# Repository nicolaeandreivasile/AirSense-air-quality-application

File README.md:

# AirSense - Air Quality Monitoring Application

## Description
We propose an application that measures the air quality in a specific location by collecting and analyzing data from the environment in real time. Air pollutants such carbon and nitrogen oxides and many others can be monitored and processed by the device. Further, data can be available to the user almost immediately. The solution is composed of three main parts:
- **embedded system**
- **mobile application**
- **persistent data storage**

## Communication
The means of communication between the two present physical devices (wearable and smartphone) are described by the GATT protocol, working over a Bluetooth Low Energy connection to minimize the power consumption regarding the transmission of data.

## Embedded system
The wearable device is the component that interacts directly with the environment, collecting data through the available sensors and transmitting it to the smartphone application for visualization. The device represents the GATT server and is structured in various modules, containing multiple components, to assure that the required functionalities are correctly implemented.

## Mobile application
The mobile application is the secondary component of the solution. Due to development requirements and available testing equipment, the Android platform is chosen as the support environment for the application. Further, it represents the GATT client, and it is designed to send requests of various types to the server and receive responses accordingly.

## Persistent data storage
Data needs to be available at any time, and not be lost due to external events. Therefore, persistent storage is implemented as a backend application with use of databases, where measurements are stored and can be accessed easily at any time throughout a backend application.

## Demo & presentation
A more detailed explanation regarding the implementation cand be found in the presentation directory. Moreover, a demo, showcasing the workflow of the proposed solution, can be found at the following link:
https://www.youtube.com/watch?v=Klh-Bsb8nCM&t=50s&ab_channel=NicolaeAndreiVasile

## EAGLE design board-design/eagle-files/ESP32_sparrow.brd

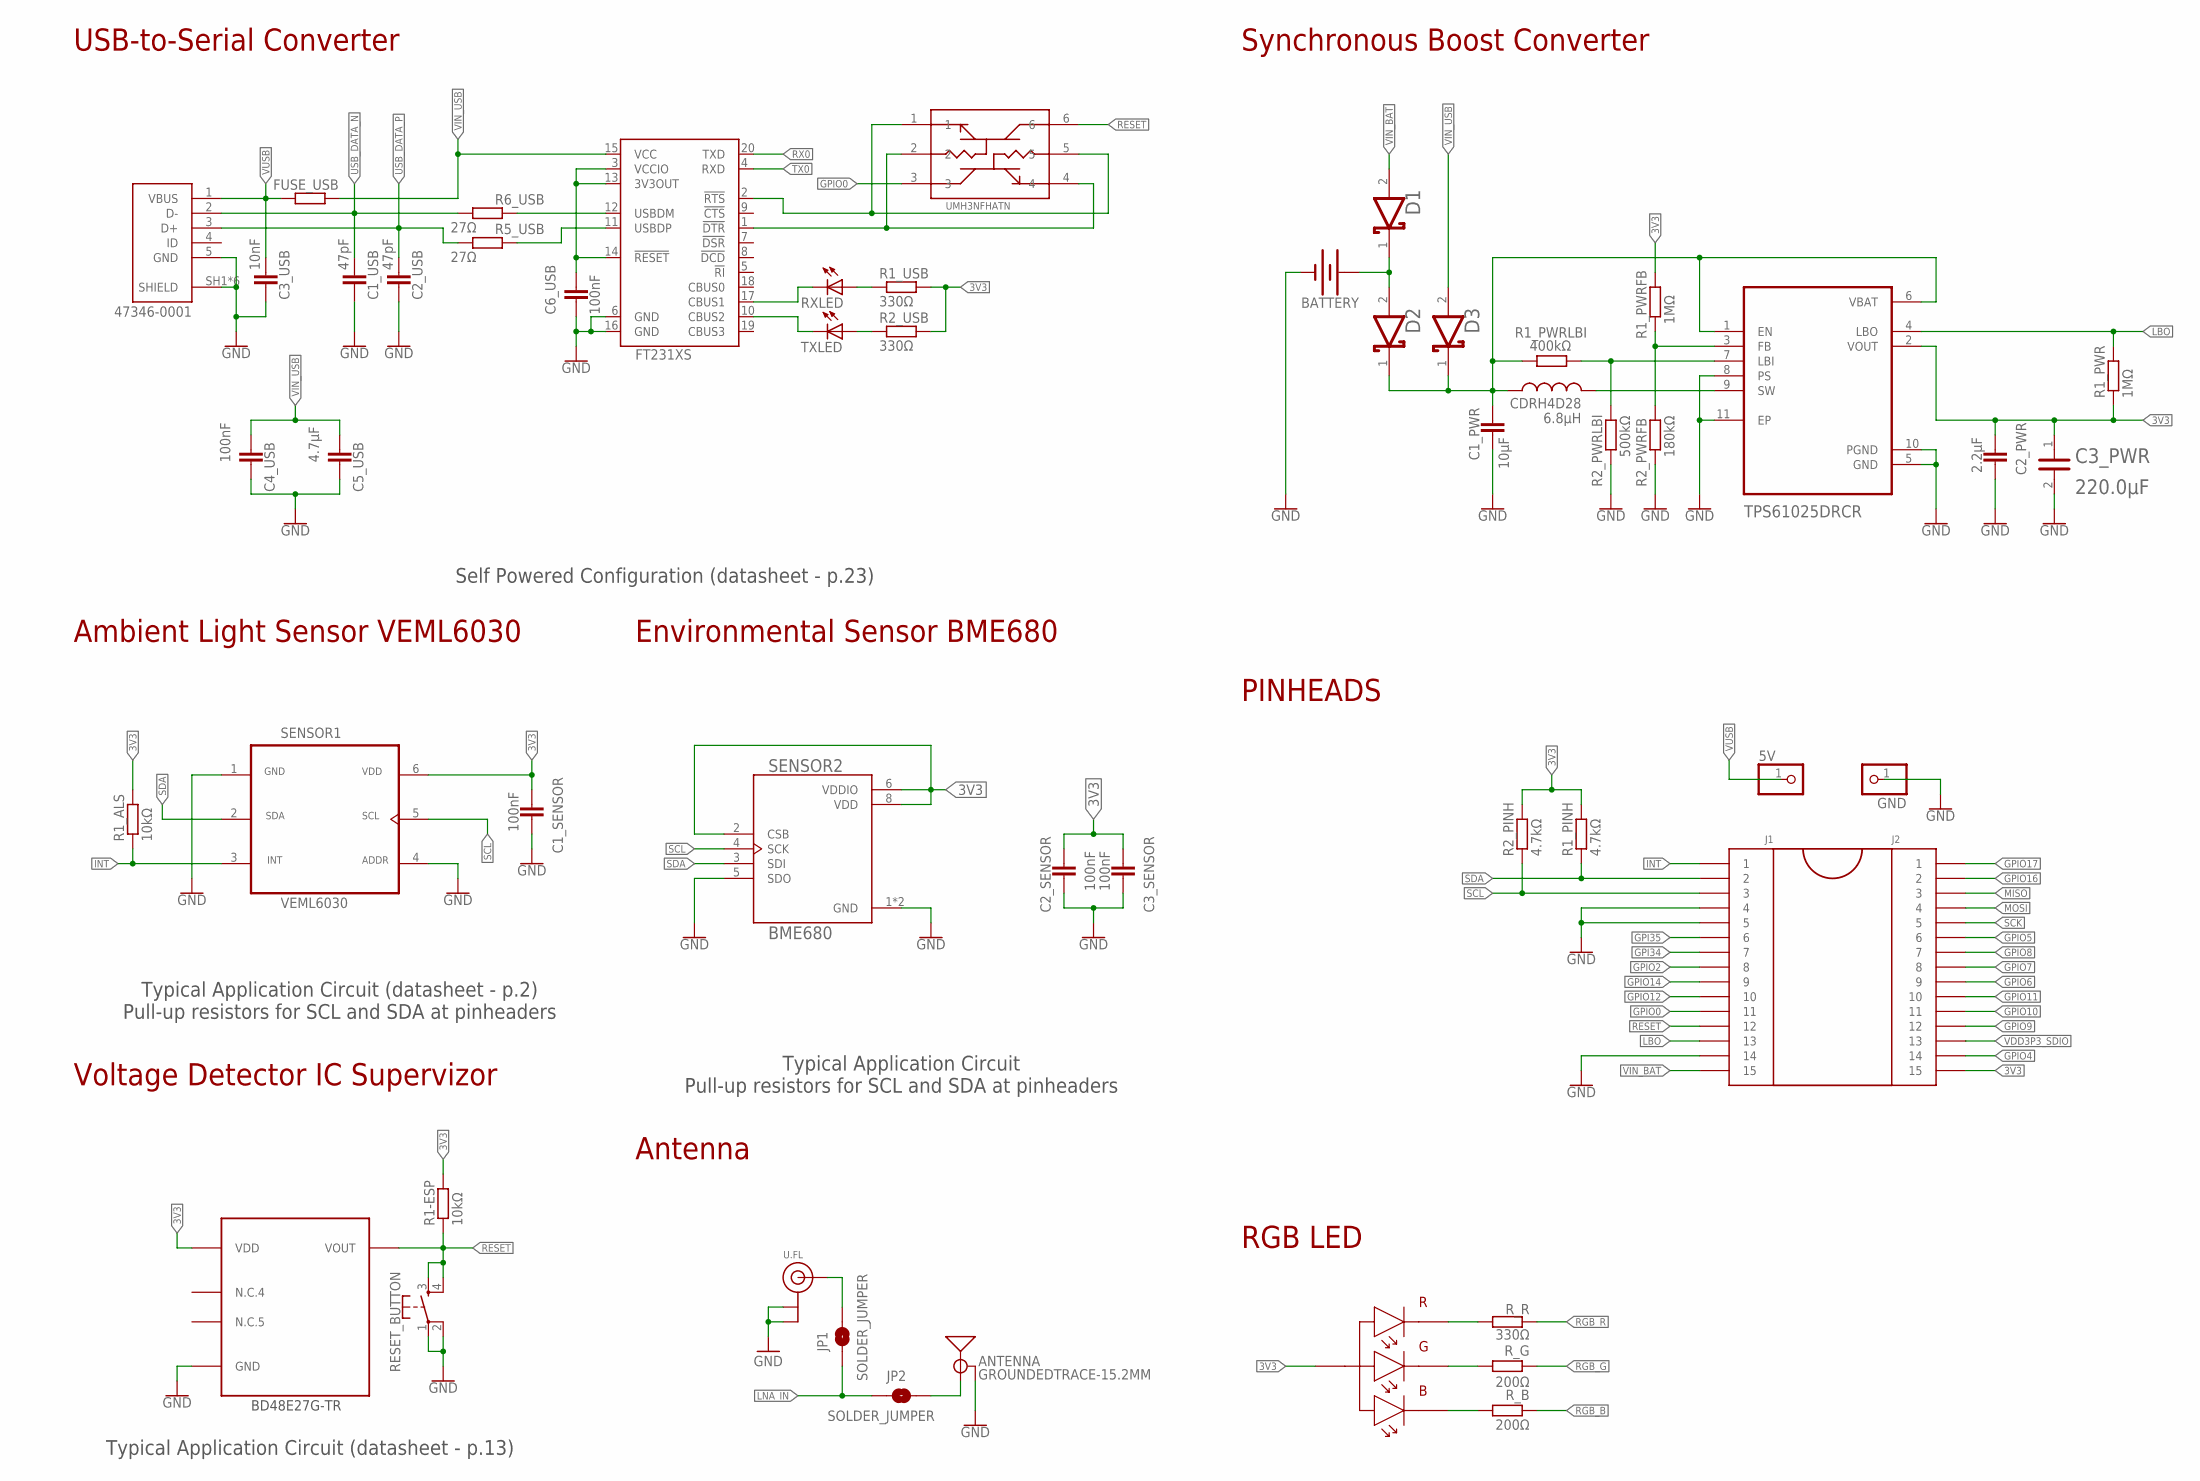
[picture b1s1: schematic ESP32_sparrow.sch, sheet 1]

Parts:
5V: PINHD-1X1; 1X01
ANTENNA: GROUNDEDTRACE-15.2MM; TRACE_ANTENNA_2.4GHZ_15.2MM
BATTERY: BATTERY-AA
BD48E27G-TR: BD48E27G-TR; SSOP5
C1_PWR: 10µF; C0402
C1_SENSOR, C2_SENSOR, C3_SENSOR, C4_USB, C6_USB: 100nF; C0402
C1_USB, C2_USB: 47pF; C0402
C2_PWR: 2.2µF; C0402
C3_PWR: SAMSUNG_ELECTRO-MECHANICS_AMERICA_CL32A227MQVNNNE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; SAMSUNG_ELECTRO-MECHANICS_AMERICA_CL32A227MQVNNNE_0
C3_USB: 10nF; C0402
C5_USB: 4.7µF; C0402
CDRH4D28: 6.8µH; INDUCTOR_CDRH4
CONVERTER: TPS61025DRCR; VREG_V62/16624-01YE
D1, D2, D3: AVX_SD0805S020S1R0AVX_SD0805S020S1R0_0_0; AVX_SD0805S020S1R0_0
FUSE_USB: PFMF.050.2; 1812X7R
GND: PINHD-1X1; 1X01
J1: HEAD15-NOSS
J2: HEAD15-NOSS-1
JP1, JP2: SOLDER_JUMPER; SMT-JUMPER_2_NO_NO-SILK
MOLEX: 47346-0001; MOLEX_47346-0001
R1-ESP, R1_ALS: 10kΩ; R0402
R1_PINH, R2_PINH: 4.7kΩ; R0402
R1_PWR, R1_PWRFB: 1MΩ; R0402
R1_PWRLBI: 400kΩ; R0402
R1_USB, R2_USB: 330Ω; R0402
R2_PWRFB: 180kΩ; R0402
R2_PWRLBI: 500kΩ; R0402
R5_USB, R6_USB: 27Ω; R0402
RESET_BUTTON: MOMENTARY-SWITCH-SPST-2-SMD-4.6X2.8MM; TACTILE_SWITCH_SMD_4.6X2.8MM
RXLED: LEDCHIP-LED0603; CHIP-LED0603
R_B: 200Ω; R0402
R_G: 200Ω; R0402
R_R: 330Ω; R0402
SENSOR1: VEML6030; VISHAY_VEML6030_2X2X0.87
SENSOR2: BME680; PSON80P300X300X100-8N
TXLED: LEDCHIP-LED0603; CHIP-LED0603
U4: FT231XS; SSOP20_L
U$1: 150202M153130-RGB; 150202M153130
U.FL: ANTENNA_U.FL; U.FL
UMH3NFHATN: UMH3NFHATN; SOP65P210X100-6N

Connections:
3V3: BD48E27G-TR.P$2 (VDD), C1_SENSOR.2, C2_PWR.2, C2_SENSOR.2, C3_PWR.1, C3_SENSOR.2, CONVERTER.2 (VOUT), J2.15, R1-ESP.2, R1_ALS.2, R1_PINH.2, R1_PWR.1, R1_PWRFB.2, R1_USB.2, R2_PINH.2, R2_USB.2, SENSOR1.6 (VDD), SENSOR2.2 (CSB), SENSOR2.6 (VDDIO), SENSOR2.8 (VDD), U$1.P$1 (1); also elsewhere on the board
GND: ANTENNA.GND, BATTERY.GND@1 (-), BD48E27G-TR.P$3 (GND), C1_PWR.1, C1_SENSOR.1, C1_USB.2, C2_PWR.1, C2_SENSOR.1, C2_USB.2, C3_PWR.2, C3_SENSOR.1, C3_USB.2, C4_USB.2, C5_USB.2, C6_USB.2, CONVERTER.5 (GND), CONVERTER.8 (PS), CONVERTER.10 (PGND), CONVERTER.11 (EP), GND.1, J1.4, J1.5, J1.14, MOLEX.5 (GND), MOLEX.SH1 (SHIELD), MOLEX.SH2 (SHIELD), MOLEX.SH3 (SHIELD), MOLEX.SH4 (SHIELD), MOLEX.SH5 (SHIELD), MOLEX.SH6 (SHIELD), R2_PWRFB.1, R2_PWRLBI.1, RESET_BUTTON.1, RESET_BUTTON.2, SENSOR1.1 (GND), SENSOR1.4 (ADDR), SENSOR2.1 (GND), SENSOR2.5 (SDO), SENSOR2.7 (GND), U4.6 (GND), U4.16 (GND), U.FL.1 (GND), U.FL.2 (GND); also elsewhere on the board
GPI34: J1.7; also elsewhere on the board
GPI35: J1.6; also elsewhere on the board
GPIO0: J1.11, UMH3NFHATN.3; also elsewhere on the board
GPIO2: J1.8; also elsewhere on the board
GPIO4: J2.14; also elsewhere on the board
GPIO5: J2.6; also elsewhere on the board
GPIO6: J2.9; also elsewhere on the board
GPIO7: J2.8; also elsewhere on the board
GPIO8: J2.7; also elsewhere on the board
GPIO9: J2.12; also elsewhere on the board
GPIO10: J2.11; also elsewhere on the board
GPIO11: J2.10; also elsewhere on the board
GPIO12: J1.10; also elsewhere on the board
GPIO14: J1.9; also elsewhere on the board
GPIO16: J2.2; also elsewhere on the board
GPIO17: J2.1; also elsewhere on the board
INT: J1.1, R1_ALS.1, SENSOR1.3 (INT); also elsewhere on the board
LBO: CONVERTER.4 (LBO), J1.13, R1_PWR.2; also elsewhere on the board
LNA_IN: JP1.1, JP2.1; also elsewhere on the board
MISO: J2.3; also elsewhere on the board
MOSI: J2.4; also elsewhere on the board
unnamed: CONVERTER.7 (LBI), R1_PWRLBI.2, R2_PWRLBI.2
unnamed: R_B.2, U$1.P$4 (4)
unnamed: R_G.2, U$1.P$3 (3)
unnamed: R_R.2, U$1.P$2 (2)
unnamed: U4.1 (!DTR), UMH3NFHATN.2, UMH3NFHATN.4
unnamed: U4.2 (!RTS), UMH3NFHATN.1, UMH3NFHATN.5
unnamed: ANTENNA.ANT (SIGNAL), JP2.2
unnamed: C6_USB.1, U4.3 (VCCIO), U4.13 (3V3OUT), U4.14 (!RESET)
unnamed: C1_PWR.2, CDRH4D28.1, CONVERTER.1 (EN), CONVERTER.6 (VBAT), D2.1 (CATHODE), D3.1 (CATHODE), R1_PWRLBI.1
unnamed: CONVERTER.3 (FB), R1_PWRFB.1, R2_PWRFB.2
unnamed: RXLED.C, U4.17 (CBUS1)
unnamed: BATTERY.PWR@1 (+), D1.1 (CATHODE), D2.2 (ANODE)
unnamed: JP1.2, U.FL.3 (SIGNAL)
unnamed: R6_USB.2, U4.12 (USBDM)
unnamed: CDRH4D28.2, CONVERTER.9 (SW)
unnamed: R1_USB.1, RXLED.A
unnamed: TXLED.C, U4.10 (CBUS2)
unnamed: R2_USB.1, TXLED.A
unnamed: R5_USB.2, U4.11 (USBDP)
RESET: BD48E27G-TR.P$1 (VOUT), J1.12, R1-ESP.1, RESET_BUTTON.3, RESET_BUTTON.4, UMH3NFHATN.6; also elsewhere on the board
RGB_B: R_B.1; also elsewhere on the board
RGB_G: R_G.1; also elsewhere on the board
RGB_R: R_R.1; also elsewhere on the board
RX0: U4.20 (TXD); also elsewhere on the board
SCK: J2.5; also elsewhere on the board
SCL: J1.3, R2_PINH.1, SENSOR1.5 (SCL), SENSOR2.4 (SCK); also elsewhere on the board
SDA: J1.2, R1_PINH.1, SENSOR1.2 (SDA), SENSOR2.3 (SDI); also elsewhere on the board
TX0: U4.4 (RXD); also elsewhere on the board
USB_DATA_N: C1_USB.1, MOLEX.2 (D-), R6_USB.1
USB_DATA_P: C2_USB.1, MOLEX.3 (D+), R5_USB.1
VDD3P3_SDIO: J2.13; also elsewhere on the board
VIN_BAT: D1.2 (ANODE), J1.15
VIN_USB: C4_USB.1, C5_USB.1, D3.2 (ANODE), FUSE_USB.2, U4.15 (VCC)
VUSB: 5V.1, C3_USB.1, FUSE_USB.1, MOLEX.1 (VBUS)

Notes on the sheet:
Self Powered Configuration (datasheet - p.23)
Typical Application Circuit (datasheet - p.2) Pull-up resistors for SCL and SDA at pinheaders
Typical Application Circuit Pull-up resistors for SCL and SDA at pinheaders
Typical Application Circuit (datasheet - p.13)
RGB LED
USB-to-Serial Converter
Synchronous Boost Converter
PINHEADS
Environmental Sensor BME680
Ambient Light Sensor VEML6030
Voltage Detector IC Supervizor
Antenna

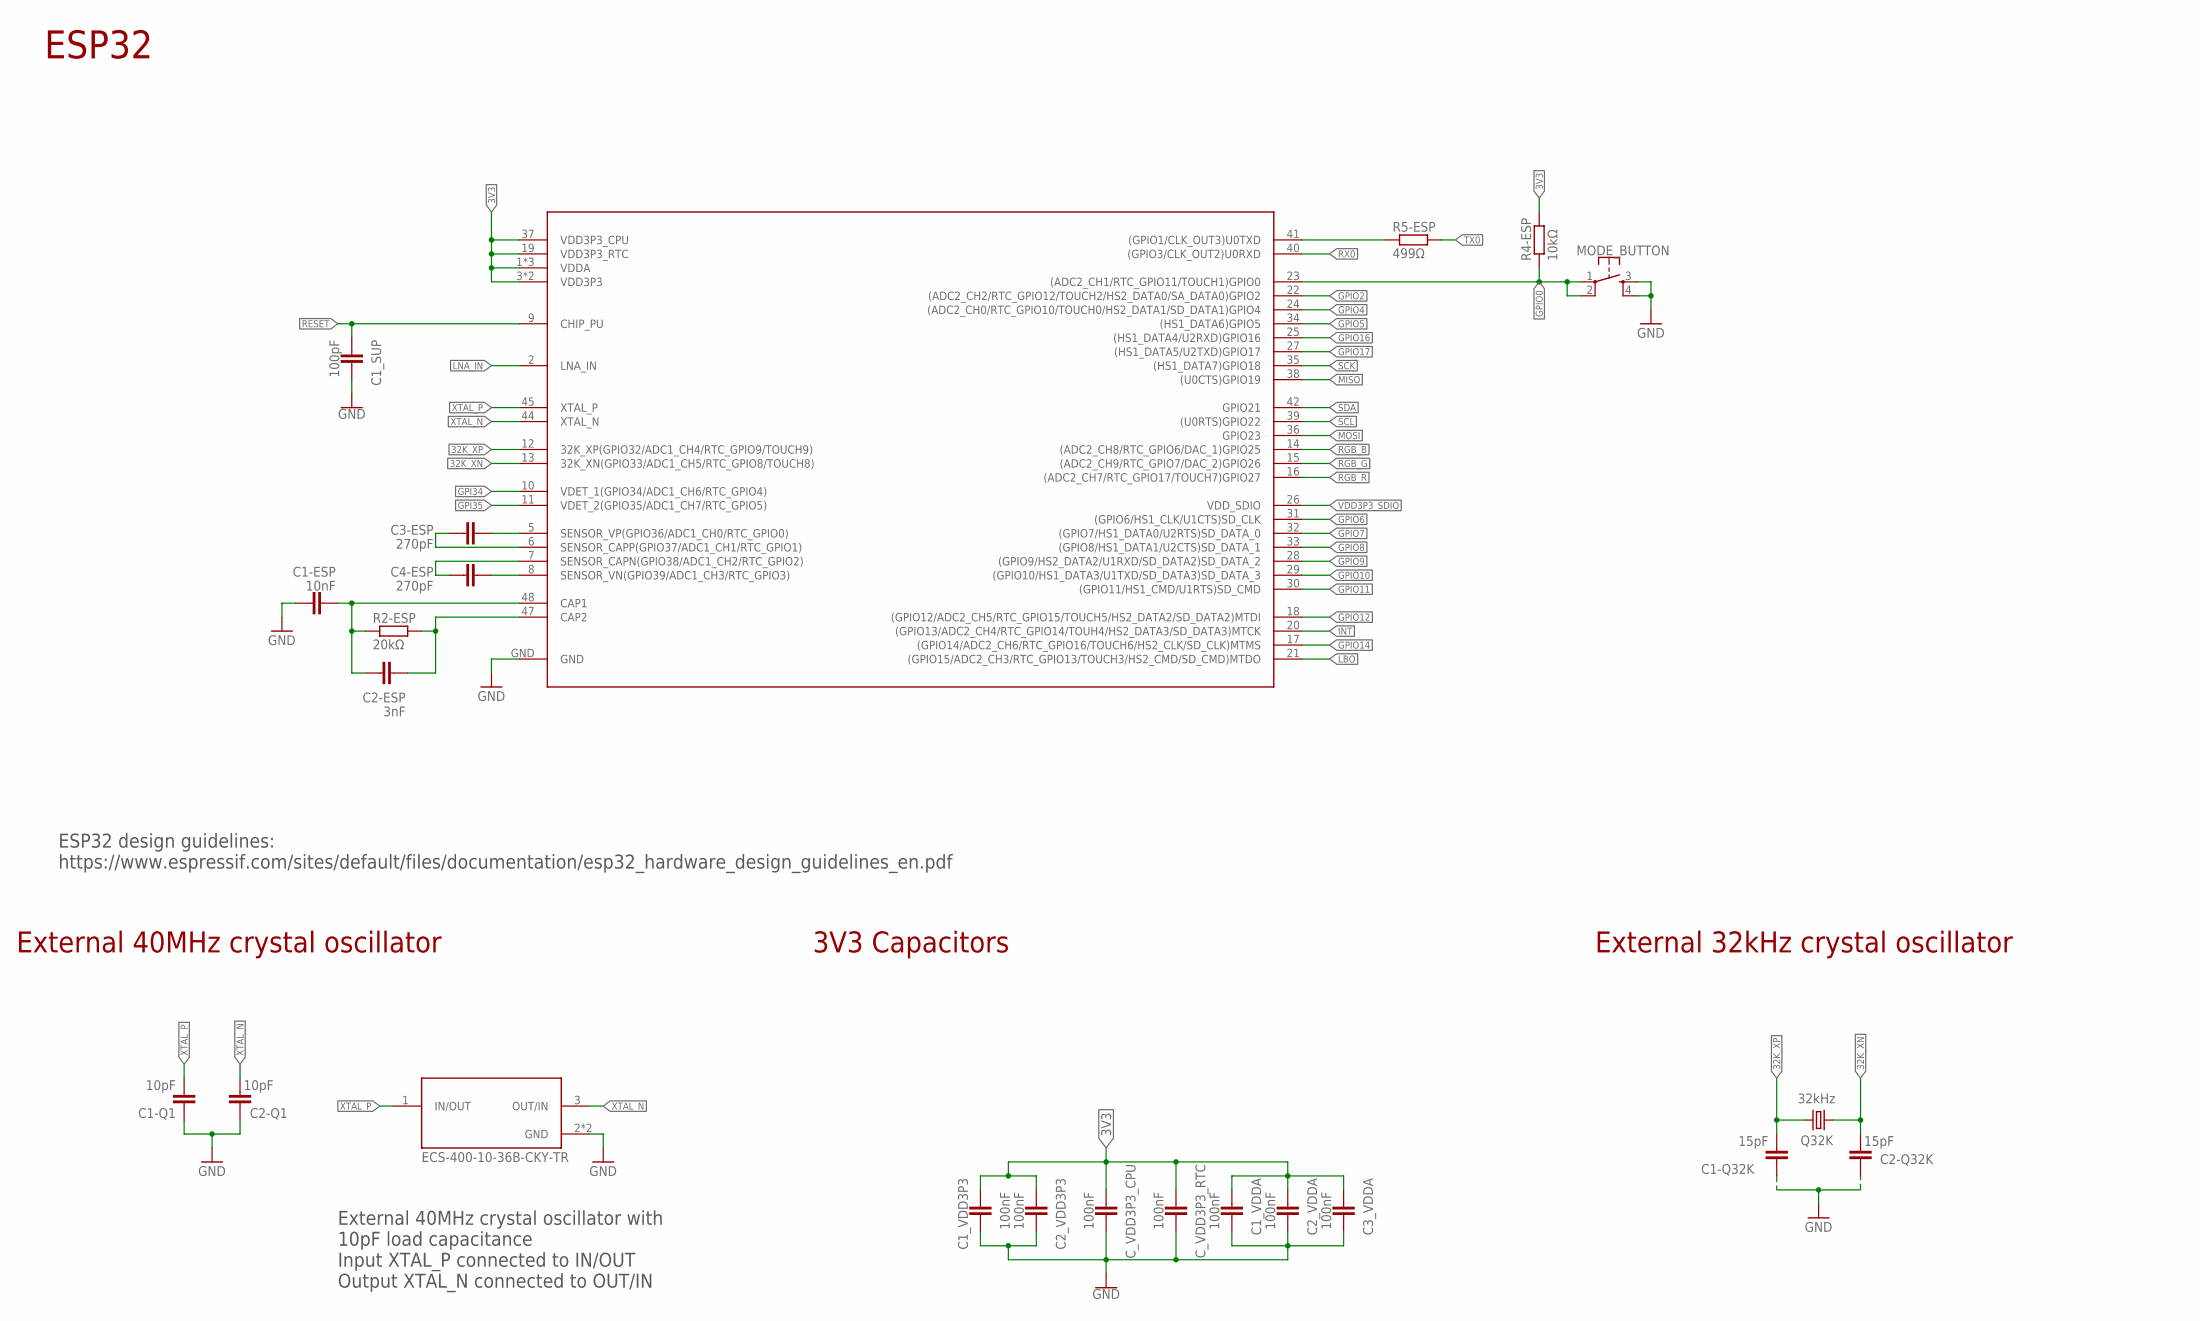
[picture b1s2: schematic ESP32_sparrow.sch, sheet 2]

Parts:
C1-ESP: 10nF; C0402
C1-Q1, C2-Q1: 10pF; C0402
C1-Q32K, C2-Q32K: 15pF; C0402
C1_SUP: 100pF; C0402
C1_VDD3P3, C1_VDDA, C2_VDD3P3, C2_VDDA, C3_VDDA: 100nF; C0402
C2-ESP: 3nF; C0402
C3-ESP, C4-ESP: 270pF; C0402
C_VDD3P3_CPU, C_VDD3P3_RTC: 100nF; C0402
MODE_BUTTON: MOMENTARY-SWITCH-SPST-2-SMD-4.6X2.8MM; TACTILE_SWITCH_SMD_4.6X2.8MM
Q32K: 32kHz; FC-12M
Q40M: ECS-400-10-36B-CKY-TR; XTAL_ECS-163.84-10-36-JGN-TR
R2-ESP: 20kΩ; R0402
R4-ESP: 10kΩ; R0402
R5-ESP: 499Ω; R0402
U$3: ESP32-U4WDH

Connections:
3V3: C1_VDD3P3.2, C1_VDDA.2, C2_VDD3P3.2, C2_VDDA.2, C3_VDDA.2, C_VDD3P3_CPU.2, C_VDD3P3_RTC.2, R4-ESP.2, U$3.1 (VDDA), U$3.3 (VDD3P3), U$3.4 (VDD3P3), U$3.19 (VDD3P3_RTC), U$3.37 (VDD3P3_CPU), U$3.43 (VDDA), U$3.46 (VDDA); also elsewhere on the board
32K_XN: C2-Q32K.2, Q32K.1, U$3.13 (32K_XN(GPIO33/ADC1_CH5/RTC_GPIO8/TOUCH8))
32K_XP: C1-Q32K.2, Q32K.2, U$3.12 (32K_XP(GPIO32/ADC1_CH4/RTC_GPIO9/TOUCH9))
GND: C1-ESP.1, C1-Q1.1, C1-Q32K.1, C1_SUP.1, C1_VDD3P3.1, C1_VDDA.1, C2-Q1.1, C2-Q32K.1, C2_VDD3P3.1, C2_VDDA.1, C3_VDDA.1, C_VDD3P3_CPU.1, C_VDD3P3_RTC.1, MODE_BUTTON.3, MODE_BUTTON.4, Q40M.2 (GND), Q40M.4 (GND), U$3.GND; also elsewhere on the board
GPI34: U$3.10 (VDET_1(GPIO34/ADC1_CH6/RTC_GPIO4)); also elsewhere on the board
GPI35: U$3.11 (VDET_2(GPIO35/ADC1_CH7/RTC_GPIO5)); also elsewhere on the board
GPIO0: MODE_BUTTON.1, MODE_BUTTON.2, R4-ESP.1, U$3.23 ((ADC2_CH1/RTC_GPIO11/TOUCH1)GPIO0); also elsewhere on the board
GPIO2: U$3.22 ((ADC2_CH2/RTC_GPIO12/TOUCH2/HS2_DATA0/S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); also elsewhere on the board
GPIO4: U$3.24 ((ADC2_CH0/RTC_GPIO10/TOUCH0/HS2_DATA1/S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); also elsewhere on the board
GPIO5: U$3.34 ((HS1_DATA6)GPIO5); also elsewhere on the board
GPIO6: U$3.31 ((GPIO6/HS1_CLK/U1CTS)SD_CLK); also elsewhere on the board
GPIO7: U$3.32 ((GPIO7/HS1_DATA0/U2RTS)SD_DATA_0); also elsewhere on the board
GPIO8: U$3.33 ((GPIO8/HS1_DATA1/U2CTS)SD_DATA_1); also elsewhere on the board
GPIO9: U$3.28 ((GPIO9/HS2_DATA2/U1RXD/SD_DATA2)SD_DATA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); also elsewhere on the board
GPIO10: U$3.29 ((GPIO10/HS1_DATA3/U1TXD/SD_DATA3)SD_DAT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); also elsewhere on the board
GPIO11: U$3.30 ((GPIO11/HS1_CMD/U1RTS)SD_CMD); also elsewhere on the board
GPIO12: U$3.18 ((GPIO12/ADC2_CH5/RTC_GPIO15/TOUCH5/HS2_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); also elsewhere on the board
GPIO14: U$3.17 ((GPIO14/ADC2_CH6/RTC_GPIO16/TOUCH6/HS2_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); also elsewhere on the board
GPIO16: U$3.25 ((HS1_DATA4/U2RXD)GPIO16); also elsewhere on the board
GPIO17: U$3.27 ((HS1_DATA5/U2TXD)GPIO17); also elsewhere on the board
INT: U$3.20 ((GPIO13/ADC2_CH4/RTC_GPIO14/TOUH4/HS2_D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); also elsewhere on the board
LBO: U$3.21 ((GPIO15/ADC2_CH3/RTC_GPIO13/TOUCH3/HS2_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); also elsewhere on the board
LNA_IN: U$3.2 (LNA_IN); also elsewhere on the board
MISO: U$3.38 ((U0CTS)GPIO19); also elsewhere on the board
MOSI: U$3.36 (GPIO23); also elsewhere on the board
unnamed: R5-ESP.1, U$3.41 ((GPIO1/CLK_OUT3)U0TXD)
unnamed: C1-ESP.2, C2-ESP.1, R2-ESP.1, U$3.48 (CAP1)
unnamed: C2-ESP.2, R2-ESP.2, U$3.47 (CAP2)
unnamed: C3-ESP.1, U$3.6 (SENSOR_CAPP(GPIO37/ADC1_CH1/RTC_GPIO1))
unnamed: C3-ESP.2, U$3.5 (SENSOR_VP(GPIO36/ADC1_CH0/RTC_GPIO0))
unnamed: C4-ESP.1, U$3.7 (SENSOR_CAPN(GPIO38/ADC1_CH2/RTC_GPIO2))
unnamed: C4-ESP.2, U$3.8 (SENSOR_VN(GPIO39/ADC1_CH3/RTC_GPIO3))
RESET: C1_SUP.2, U$3.9 (CHIP_PU); also elsewhere on the board
RGB_B: U$3.14 ((ADC2_CH8/RTC_GPIO6/DAC_1)GPIO25); also elsewhere on the board
RGB_G: U$3.15 ((ADC2_CH9/RTC_GPIO7/DAC_2)GPIO26); also elsewhere on the board
RGB_R: U$3.16 ((ADC2_CH7/RTC_GPIO17/TOUCH7)GPIO27); also elsewhere on the board
RX0: U$3.40 ((GPIO3/CLK_OUT2)U0RXD); also elsewhere on the board
SCK: U$3.35 ((HS1_DATA7)GPIO18); also elsewhere on the board
SCL: U$3.39 ((U0RTS)GPIO22); also elsewhere on the board
SDA: U$3.42 (GPIO21); also elsewhere on the board
TX0: R5-ESP.2; also elsewhere on the board
VDD3P3_SDIO: U$3.26 (VDD_SDIO); also elsewhere on the board
XTAL_N: C2-Q1.2, Q40M.3 (OUT/IN), U$3.44 (XTAL_N)
XTAL_P: C1-Q1.2, Q40M.1 (IN/OUT), U$3.45 (XTAL_P)

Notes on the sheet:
External 40MHz crystal oscillator with 10pF load capacitance Input XTAL_P connected to IN/OUT Output XTAL_N connected to OUT/IN
ESP32
External 40MHz crystal oscillator
3V3 Capacitors
External 32kHz crystal oscillator
ESP32 design guidelines: https://www.espressif.com/sites/default/files/documentation/esp32_hardware_design_guidelines_en.pdf

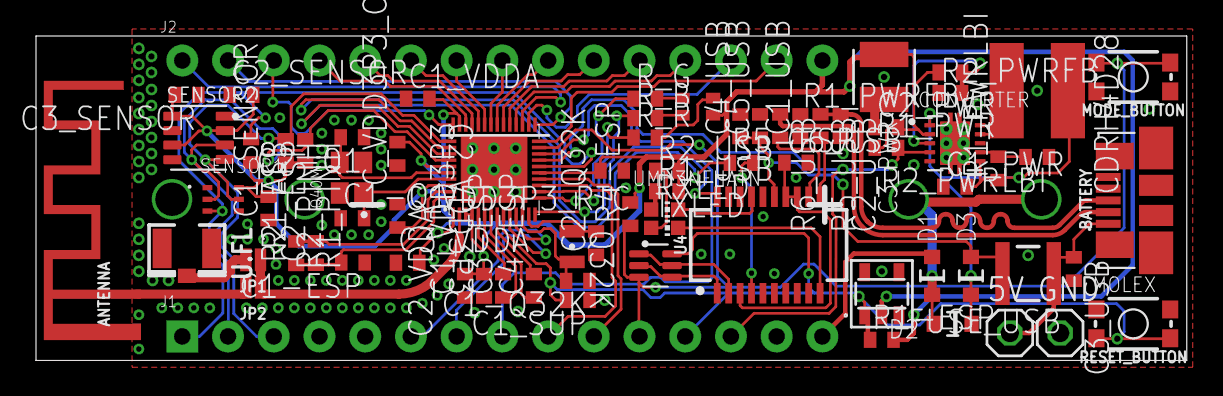
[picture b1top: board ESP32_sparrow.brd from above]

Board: 2 copper layers, 63.9 x 18.0 mm, 76 parts (0 on the bottom side), 68 nets.

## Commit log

2021-10-18 Initial files added
2021-10-18 README.md created
2021-10-18 README.md & presentation refactored

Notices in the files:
parts and their libraries:
SparkFun-RF: Licensing: Creative Commons ShareAlike 4.0 International - https://creativecommons.org/licenses/by-sa/4.0
m-pad-2.1: License : GNU General Public License version 2 (see bottom)
